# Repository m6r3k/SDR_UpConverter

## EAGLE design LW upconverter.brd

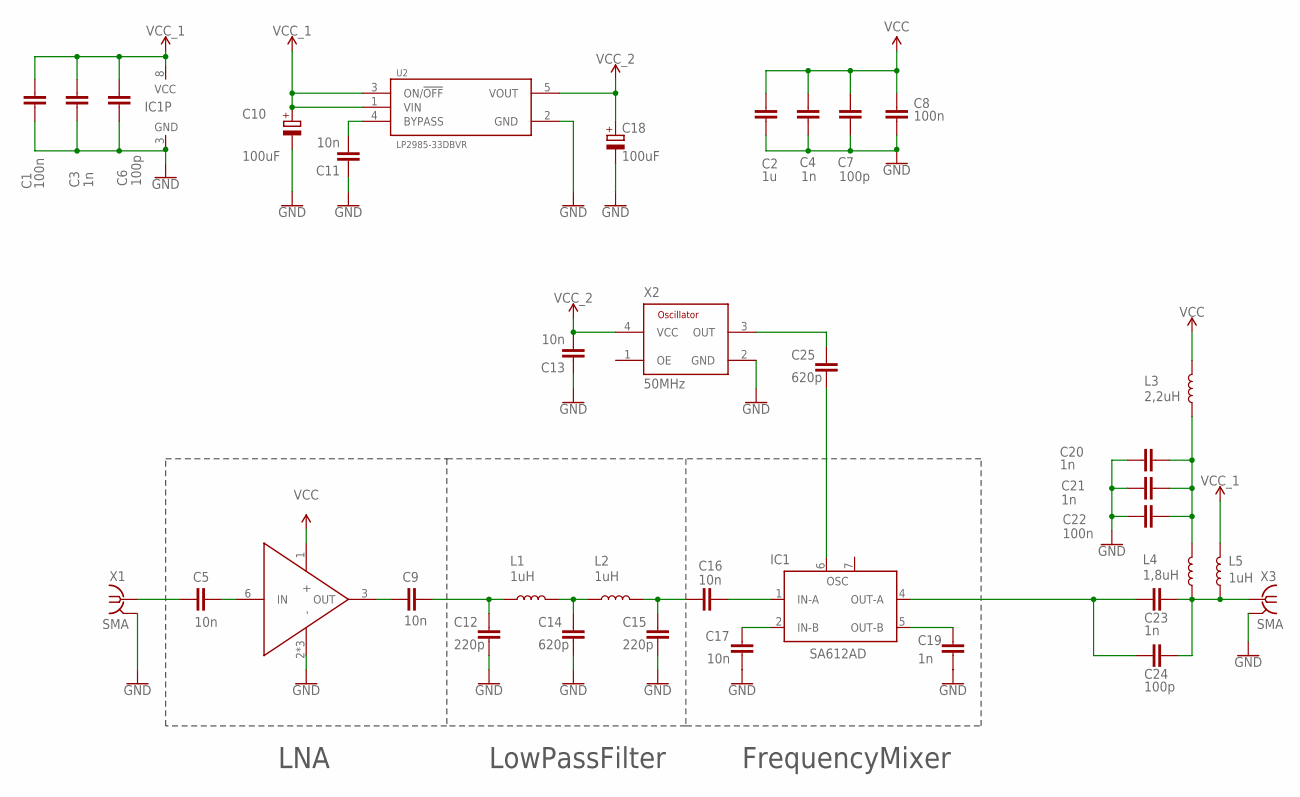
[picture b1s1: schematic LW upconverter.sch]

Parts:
C1, C8, C22: 100n; C0603K
C2: 1u; C0603K
C3, C4, C19, C20, C21, C23: 1n; C0603K
C5, C9, C11, C13, C16, C17: 10n; C0603K
C6, C7, C24: 100p; C0603K
C10, C18: 100uF; CT3528
C12, C15: 220p; C0603K
C14, C25: 620p; C0603K
IC1: SA612AD; SO08
L1, L2, L5: 1uH; 0603
L3: 2,2uH; 0603
L4: 1,8uH; 0603
U1: BGA28XX_BGA28XX; BGA28XX_SOT363_PHILIPS
U2: LP2985-33DBVR; SOT95P280X145-5N
X1, X3: SMA; J502-ND-142-0711-881/886
X2: 50MHz; ASF1_ASFL_ASFL1

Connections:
GND: C1.2, C2.2, C3.2, C4.2, C6.2, C7.2, C8.1, C10.-, C11.1, C12.1, C13.1, C14.1, C15.1, C17.1, C18.-, C19.1, C20.2, C21.2, C22.2, IC1.3 (GND), U1.2 (-), U1.4 (-), U1.5 (-), U2.2 (GND), X1.G@1 (2), X1.G@2 (2), X1.G@3 (2), X1.G@4 (2), X2.2 (GND), X3.G@1 (2), X3.G@2 (2), X3.G@3 (2), X3.G@4 (2)
unnamed: C23.1, C24.1, L4.1, L5.1, X3.1
unnamed: C14.2, L1.2, L2.1
unnamed: C15.2, C16.2, L2.2
unnamed: C17.2, IC1.2 (IN-B)
unnamed: C19.2, IC1.5 (OUT-B)
unnamed: C23.2, C24.2, IC1.4 (OUT-A)
unnamed: C9.1, U1.3 (OUT)
unnamed: C16.1, IC1.1 (IN-A)
unnamed: C5.2, U1.6 (IN)
unnamed: C5.1, X1.1
unnamed: C9.2, C12.2, L1.1
unnamed: C20.1, C21.1, C22.1, L3.1, L4.2
unnamed: C11.2, U2.4 (BYPASS)
unnamed: C25.2, X2.3 (OUT)
unnamed: C25.1, IC1.6 (OSC)
VCC: C2.1, C4.1, C7.1, C8.2, L3.2, U1.1 (+)
VCC_1: C1.1, C3.1, C6.1, C10.+, IC1.8 (VCC), L5.2, U2.1 (VIN), U2.3 (ON/!OFF)
VCC_2: C13.2, C18.+, U2.5 (VOUT), X2.4 (VCC)

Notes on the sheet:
LNA
LowPassFilter
FrequencyMixer

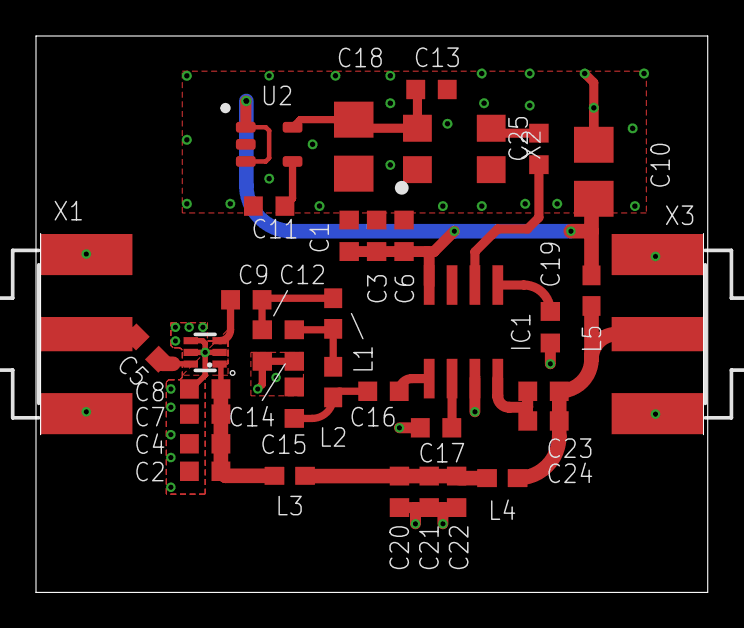
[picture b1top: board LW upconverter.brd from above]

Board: 2 copper layers, 37.3 x 30.9 mm, 36 parts (0 on the bottom side), 19 nets.

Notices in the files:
parts and their libraries:
PowerPack_PAD: License : GNU General Public License version 2 (see bottom)
SparkFun-Coils: Licensing: Creative Commons ShareAlike 4.0 International - https://creativecommons.org/licenses/by-sa/4.0
